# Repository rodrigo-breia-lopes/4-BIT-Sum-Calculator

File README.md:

# 4-BIT-Sum-Calculator
Tried PCB design for the first time

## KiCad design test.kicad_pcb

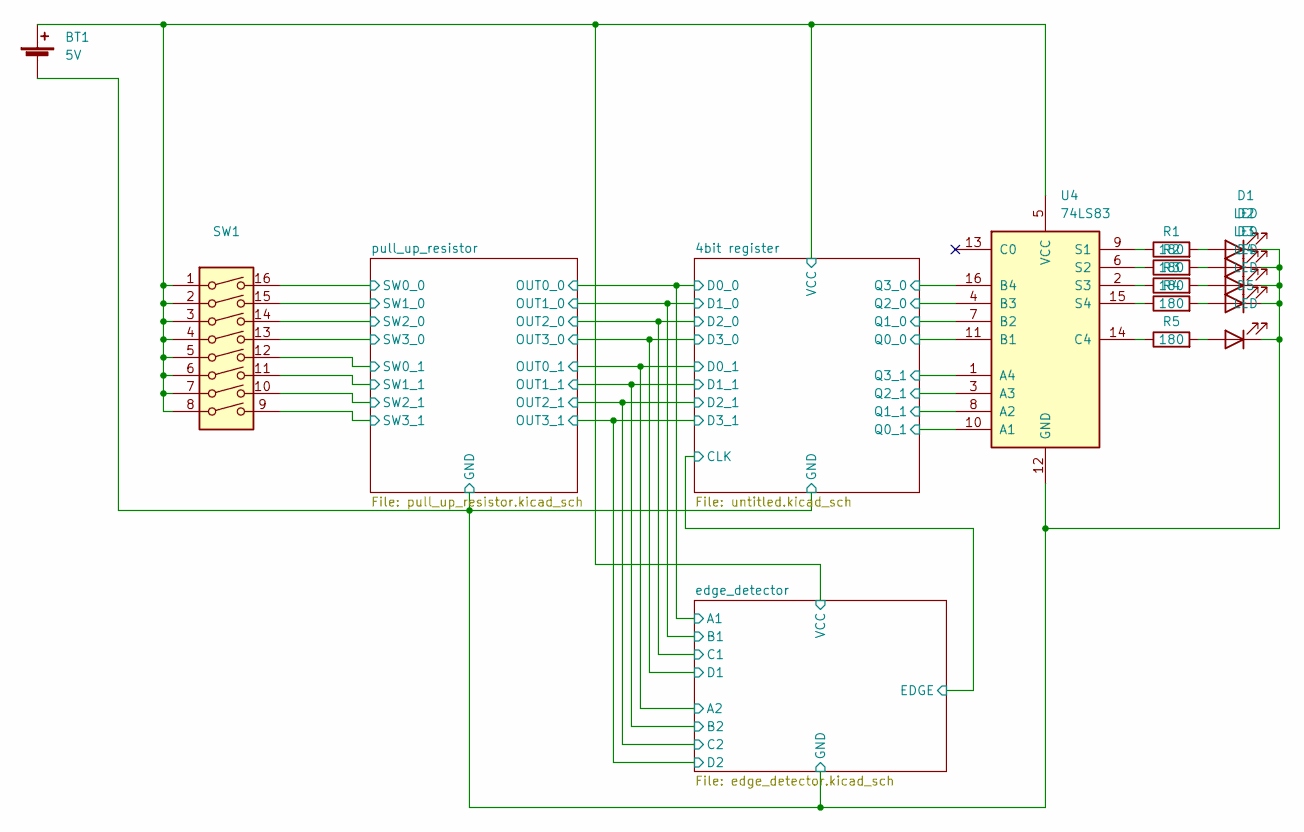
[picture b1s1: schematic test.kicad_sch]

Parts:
BT1: 5V; PinHeader_1x02_P2.54mm_Vertical
D1, D2, D3, D4, D5: LED; D_DO-15_P2.54mm_Vertical_KathodeUp
R1, R2, R3, R4, R5: 180; R_Axial_DIN0204_L3.6mm_D1.6mm_P5.08mm_Horizontal
SW1: (no value)
U4: 74LS83; DIP-16_W7.62mm_Socket

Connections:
/4bit register/D0_0: SW1.16; also elsewhere on the board
/4bit register/D0_1: SW1.12; also elsewhere on the board
/4bit register/D1_0: SW1.15; also elsewhere on the board
/4bit register/D1_1: SW1.11; also elsewhere on the board
/4bit register/D2_0: SW1.14; also elsewhere on the board
/4bit register/D2_1: SW1.10; also elsewhere on the board
/4bit register/D3_0: SW1.13; also elsewhere on the board
/4bit register/D3_1: SW1.9; also elsewhere on the board
/4bit register/GND: BT1.2 (-), D1.1 (K), D2.1 (K), D3.1 (K), D4.1 (K), D5.1 (K), U4.12 (GND); also elsewhere on the board
/4bit register/Q0_0: U4.11 (B1); also elsewhere on the board
/4bit register/Q0_1: U4.10 (A1); also elsewhere on the board
/4bit register/Q1_0: U4.7 (B2); also elsewhere on the board
/4bit register/Q1_1: U4.8 (A2); also elsewhere on the board
/4bit register/Q2_0: U4.4 (B3); also elsewhere on the board
/4bit register/Q2_1: U4.3 (A3); also elsewhere on the board
/4bit register/Q3_0: U4.16 (B4); also elsewhere on the board
/4bit register/Q3_1: U4.1 (A4); also elsewhere on the board
/4bit register/VCC: BT1.1 (+), SW1.1, SW1.2, SW1.3, SW1.4, SW1.5, SW1.6, SW1.7, SW1.8, U4.5 (VCC); also elsewhere on the board
unnamed: D1.2 (A), R1.2
unnamed: D2.2 (A), R2.2
unnamed: D3.2 (A), R3.2
unnamed: D4.2 (A), R4.2
unnamed: D5.2 (A), R5.2
unnamed: R1.1, U4.9 (S1)
unnamed: R2.1, U4.6 (S2)
unnamed: R3.1, U4.2 (S3)
unnamed: R4.1, U4.15 (S4)
unnamed: R5.1, U4.14 (C4)

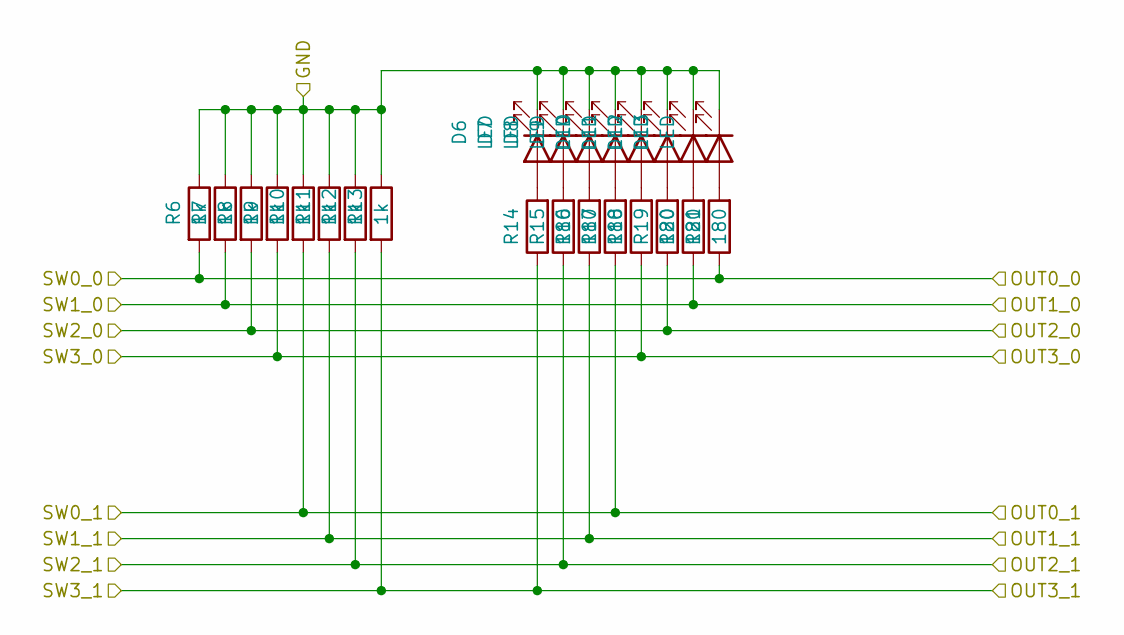
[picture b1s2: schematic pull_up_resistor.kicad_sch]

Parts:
D6, D7, D8, D9, D10, D11, D12, D13: LED; D_DO-15_P2.54mm_Vertical_KathodeUp
R6, R7, R8, R9, R10, R11, R12, R13: 1k; R_Axial_DIN0204_L3.6mm_D1.6mm_P5.08mm_Horizontal
R14, R18: (no value)
R15, R16, R17, R19, R20, R21: 180; R_Axial_DIN0204_L3.6mm_D1.6mm_P5.08mm_Horizontal

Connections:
/4bit register/D0_0: R6.2, R21.1; also elsewhere on the board
/4bit register/D0_1: R10.2, R17.1; also elsewhere on the board
/4bit register/D1_0: R7.2, R20.1; also elsewhere on the board
/4bit register/D1_1: R11.2, R16.1; also elsewhere on the board
/4bit register/D2_0: R8.2, R19.1; also elsewhere on the board
/4bit register/D2_1: R12.2, R15.1; also elsewhere on the board
/4bit register/D3_0: R9.2, R18.1; also elsewhere on the board
/4bit register/D3_1: R13.2, R14.1; also elsewhere on the board
/4bit register/GND: D6.1 (K), D7.1 (K), D8.1 (K), D9.1 (K), D10.1 (K), D11.1 (K), D12.1 (K), D13.1 (K), R6.1, R7.1, R8.1, R9.1, R10.1, R11.1, R12.1, R13.1; also elsewhere on the board
unnamed: D6.2 (A), R14.2
unnamed: D7.2 (A), R15.2
unnamed: D8.2 (A), R16.2
unnamed: D9.2 (A), R17.2
unnamed: D10.2 (A), R18.2
unnamed: D11.2 (A), R19.2
unnamed: D12.2 (A), R20.2
unnamed: D13.2 (A), R21.2

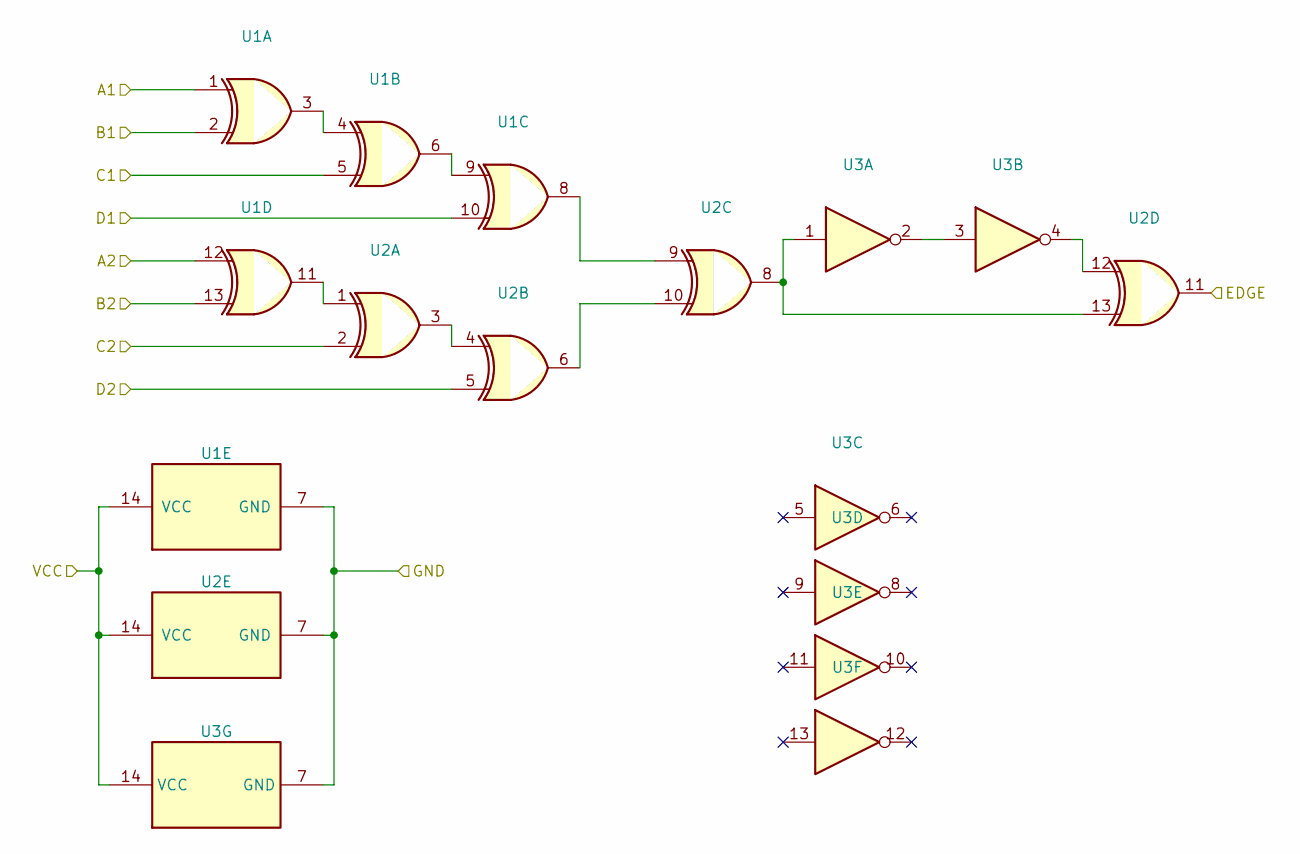
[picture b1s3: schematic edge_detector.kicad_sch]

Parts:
U1, U2: DIP-14_W7.62mm_Socket
U3: (no value)

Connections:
/4bit register/CLK: U2.11; also elsewhere on the board
/4bit register/D0_0: U1.1; also elsewhere on the board
/4bit register/D0_1: U1.12; also elsewhere on the board
/4bit register/D1_0: U1.2; also elsewhere on the board
/4bit register/D1_1: U1.13; also elsewhere on the board
/4bit register/D2_0: U1.5; also elsewhere on the board
/4bit register/D2_1: U2.2; also elsewhere on the board
/4bit register/D3_0: U1.10; also elsewhere on the board
/4bit register/D3_1: U2.5; also elsewhere on the board
/4bit register/GND: U1.7 (GND), U2.7 (GND), U3.7 (GND); also elsewhere on the board
/4bit register/VCC: U1.14 (VCC), U2.14 (VCC), U3.14 (VCC); also elsewhere on the board
unnamed: U1.3, U1.4
unnamed: U1.6, U1.9
unnamed: U1.8, U2.9
unnamed: U1.11, U2.1
unnamed: U2.3, U2.4
unnamed: U2.6, U2.10
unnamed: U2.12, U3.4
unnamed: U2.8, U2.13, U3.1
unnamed: U3.2, U3.3

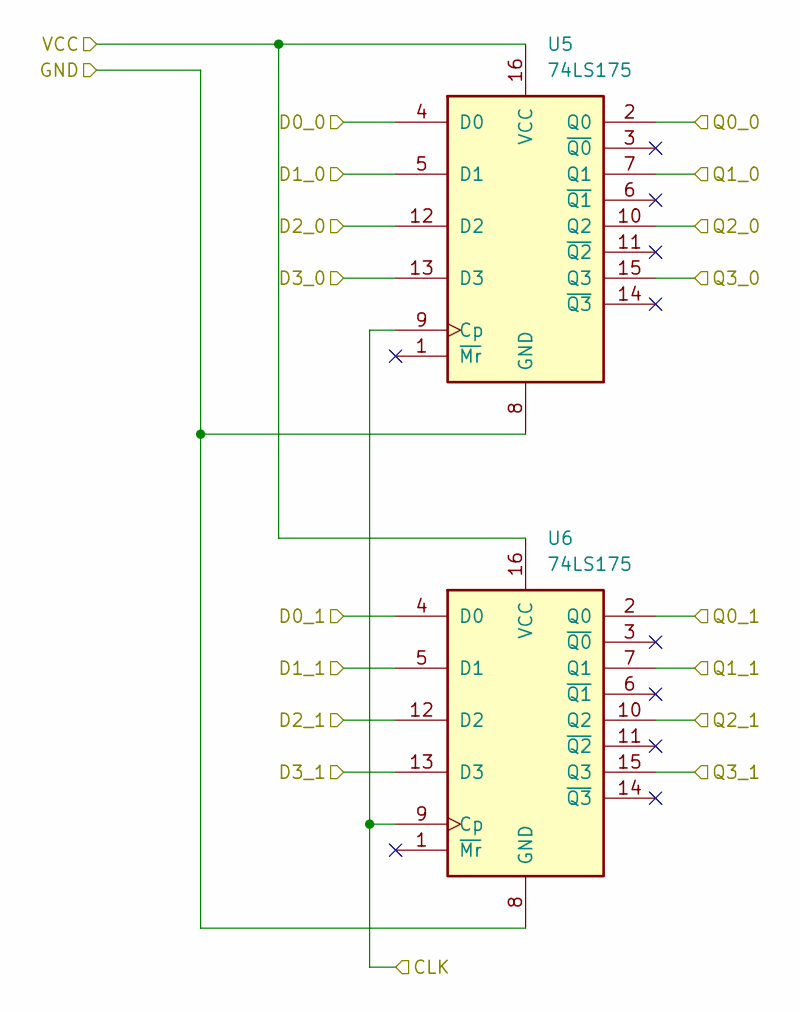
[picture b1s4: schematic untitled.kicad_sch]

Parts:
U5, U6: 74LS175; DIP-16_W7.62mm_Socket

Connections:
/4bit register/CLK: U5.9 (Cp), U6.9 (Cp); also elsewhere on the board
/4bit register/D0_0: U5.4 (D0); also elsewhere on the board
/4bit register/D0_1: U6.4 (D0); also elsewhere on the board
/4bit register/D1_0: U5.5 (D1); also elsewhere on the board
/4bit register/D1_1: U6.5 (D1); also elsewhere on the board
/4bit register/D2_0: U5.12 (D2); also elsewhere on the board
/4bit register/D2_1: U6.12 (D2); also elsewhere on the board
/4bit register/D3_0: U5.13 (D3); also elsewhere on the board
/4bit register/D3_1: U6.13 (D3); also elsewhere on the board
/4bit register/GND: U5.8 (GND), U6.8 (GND); also elsewhere on the board
/4bit register/Q0_0: U5.2 (Q0); also elsewhere on the board
/4bit register/Q0_1: U6.2 (Q0); also elsewhere on the board
/4bit register/Q1_0: U5.7 (Q1); also elsewhere on the board
/4bit register/Q1_1: U6.7 (Q1); also elsewhere on the board
/4bit register/Q2_0: U5.10 (Q2); also elsewhere on the board
/4bit register/Q2_1: U6.10 (Q2); also elsewhere on the board
/4bit register/Q3_0: U5.15 (Q3); also elsewhere on the board
/4bit register/Q3_1: U6.15 (Q3); also elsewhere on the board
/4bit register/VCC: U5.16 (VCC), U6.16 (VCC); also elsewhere on the board

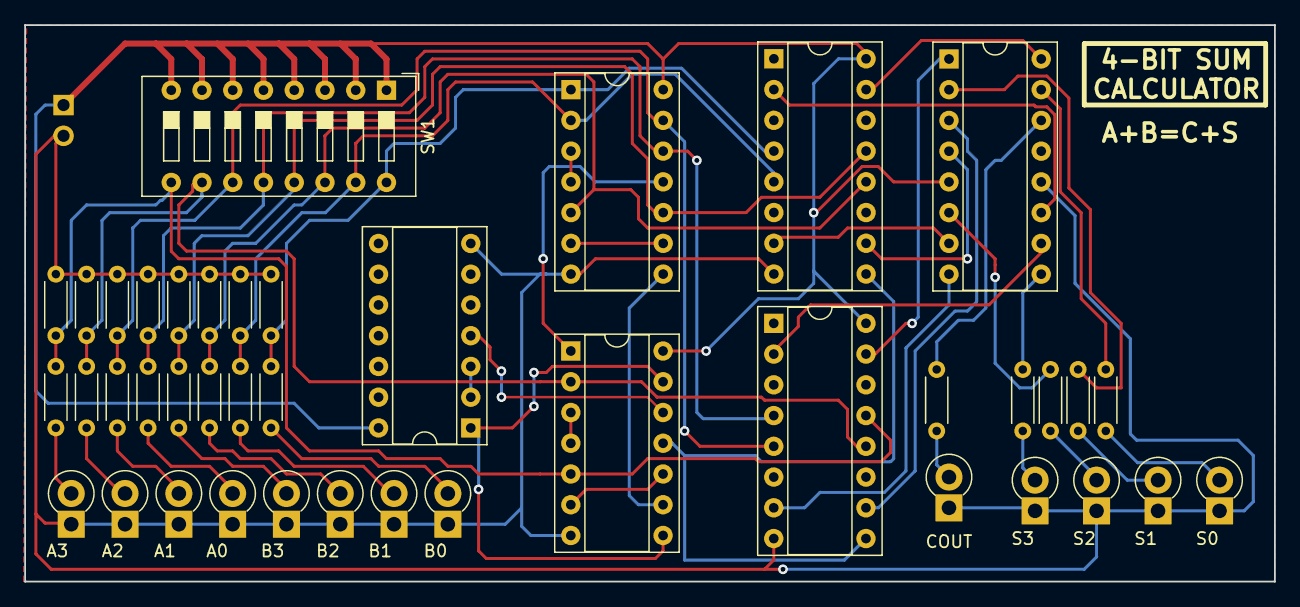
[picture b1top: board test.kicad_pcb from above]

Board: 2 copper layers, 103.3 x 46.0 mm, 42 parts (1 on the bottom side), 46 nets.

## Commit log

2022-04-08 initial
